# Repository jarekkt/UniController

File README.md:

# UniController

This is a off-spin from my commercial controller for industrial ink printers.
It is designed for pick & place machines controlled by OpenPnp

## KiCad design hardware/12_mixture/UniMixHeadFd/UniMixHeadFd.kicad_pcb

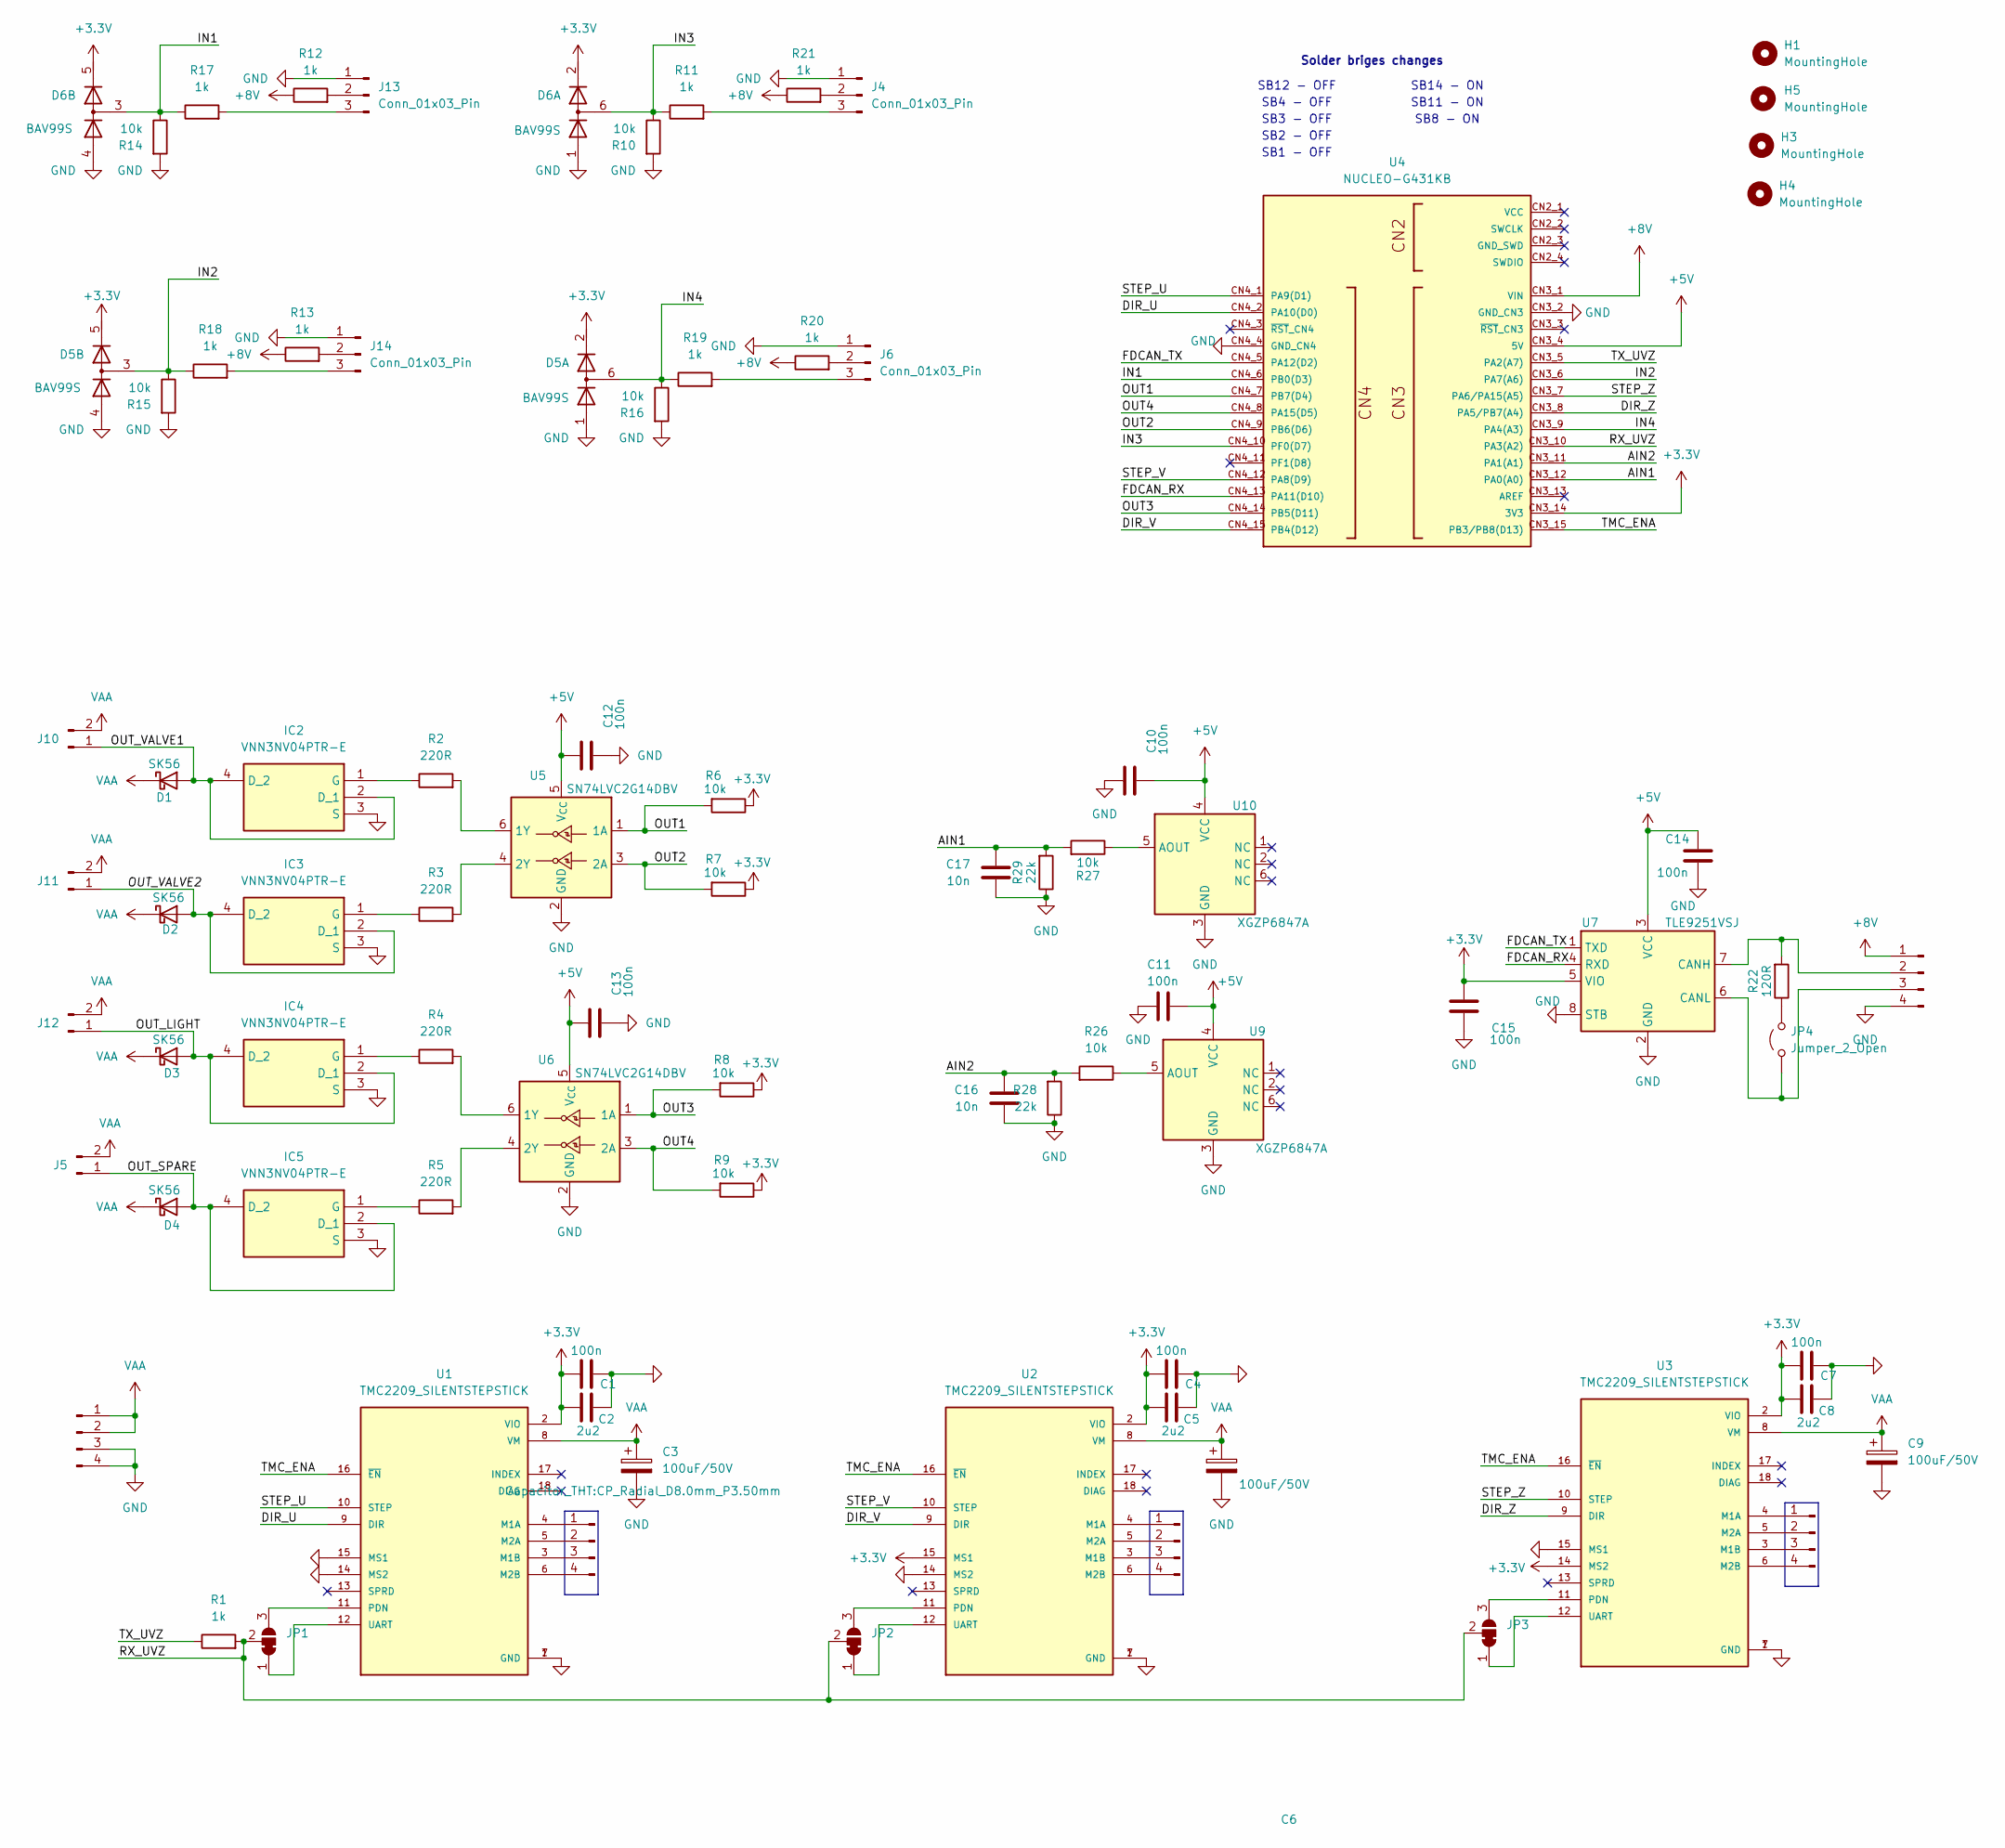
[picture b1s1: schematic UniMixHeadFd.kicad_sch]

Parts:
C1, C4, C7, C10, C11, C12, C13, C15: 100n; C_0603_1608Metric
C2, C5, C8: 2u2; C_0603_1608Metric
C3, C6, C9: 100uF/50V; CP_Radial_D8.0mm_P3.50mm
C14: 100n; C_0603_1608Metric; Digikey CC0402KRX7R7BB104
C16, C17: 10n; C_0603_1608Metric
D1, D2, D3, D4: SK56; D_SMB
D5, D6: BAV99S; SOT-363_SC-70-6
H1, H3, H4, H5: MountingHole; MountingHole_3.2mm_M3
IC2, IC3, IC4, IC5: VNN3NV04PTR-E; SOT230P700X180-4N; Manufacturer_Part_Number VNN3NV04PTR-E; Mouser Part Number 511-VNN3NV04PTR-E
J1, J2, J3, J25, J26: Conn_01x04_Male; JST_XH_B4B-XH-AM_1x04_P2.50mm_Vertical
J4, J6, J13, J14: Conn_01x03_Pin; JST_XH_B3B-XH-A_1x03_P2.50mm_Vertical
J5, J10, J11, J12: Conn_01x02_Male; JST_XH_B2B-XH-A_1x02_P2.50mm_Vertical
JP1, JP2, JP3: SolderJumper_3_Bridged12; SolderJumper-3_P1.3mm_Bridged12_RoundedPad1.0x1.5mm
JP4: Jumper_2_Open; SolderJumper-2_P1.3mm_Open_RoundedPad1.0x1.5mm
R1, R11, R12, R13, R17, R18, R19, R20, R21: 1k; R_0603_1608Metric
R2, R3, R4, R5: 220R; R_0603_1608Metric
R6, R7, R8, R9, R10, R14, R15, R16, R26, R27: 10k; R_0603_1608Metric
R22: 120R; R_1206_3216Metric
R28, R29: 22k; R_0603_1608Metric
U1, U2, U3: TMC2209_SILENTSTEPSTICK; MODULE_TMC2209_SILENTSTEPSTICK; PARTREV 1.20
U4: NUCLEO-G431KB; MODULE_NUCLEO-G431KB; PARTREV 2
U5, U6: SN74LVC2G14DBV; SOT-23-6
U7: TLE9251VSJ; SOIC-8_3.9x4.9mm_P1.27mm; Digikey TLE9251VSJXUMA1TR-ND
U9, U10: XGZP6847A; DIP-6_W10.16mm

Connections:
+3.3V: C1.2, C2.2, C4.2, C5.2, C7.2, C8.2, C15.1, D5.2 (K2), D5.5 (K4), D6.2 (K2), D6.5 (K4), R6.1, R7.1, R8.1, R9.1, U1.2 (VIO), U2.2 (VIO), U2.15 (MS1), U3.2 (VIO), U3.14 (MS2), U4.CN3_14 (3V3), U7.5 (VIO)
+5V: C10.2, C11.1, C12.1, C13.1, C14.1, U4.CN3_4 (5V), U5.5 (V_{CC}), U6.5 (V_{CC}), U7.3 (VCC), U9.4 (VCC), U10.4 (VCC)
+8V: J26.1, R12.1, R13.1, R20.1, R21.1, U4.CN3_1 (VIN)
/AIN1: C17.1, R27.2, R29.2, U4.CN3_12 (PA0(A0))
/AIN2: C16.1, R26.2, R28.2, U4.CN3_11 (PA1(A1))
/DIR_U: U1.9 (DIR), U4.CN4_2 (PA10(D0))
/DIR_V: U2.9 (DIR), U4.CN4_15 (PB4(D12))
/DIR_Z: U3.9 (DIR), U4.CN3_8 (PA5/PB7(A4))
/FDCAN_RX: U4.CN4_13 (PA11(D10)), U7.4 (RXD)
/FDCAN_TX: U4.CN4_5 (PA12(D2)), U7.1 (TXD)
/IN1: D6.3 (K1A2), R14.1, R17.1, U4.CN4_6 (PB0(D3))
/IN2: D5.3 (K1A2), R15.1, R18.1, U4.CN3_6 (PA7(A6))
/IN3: D6.6 (K3A4), R10.1, R11.1, U4.CN4_10 (PF0(D7))
/IN4: D5.6 (K3A4), R16.1, R19.1, U4.CN3_9 (PA4(A3))
/OUT1: R6.2, U4.CN4_7 (PB7(D4)), U5.1 (1A)
/OUT2: R7.2, U4.CN4_9 (PB6(D6)), U5.3 (2A)
/OUT3: R8.2, U4.CN4_14 (PB5(D11)), U6.1 (1A)
/OUT4: R9.2, U4.CN4_8 (PA15(D5)), U6.3 (2A)
/OUT_LIGHT: D3.2 (A), IC4.2 (D_1), IC4.4 (D_2), J12.1
/OUT_SPARE: D4.2 (A), IC5.2 (D_1), IC5.4 (D_2), J5.1
/OUT_VALVE1: D1.2 (A), IC2.2 (D_1), IC2.4 (D_2), J10.1
/OUT_VALVE2: D2.2 (A), IC3.2 (D_1), IC3.4 (D_2), J11.1
/RX_UVZ: JP1.2 (C), JP2.2 (C), JP3.2 (C), R1.2, U4.CN3_10 (PA3(A2))
/STEP_U: U1.10 (STEP), U4.CN4_1 (PA9(D1))
/STEP_V: U2.10 (STEP), U4.CN4_12 (PA8(D9))
/STEP_Z: U3.10 (STEP), U4.CN3_7 (PA6/PA15(A5))
/TMC_ENA: U1.16 (~EN), U2.16 (~EN), U3.16 (~EN), U4.CN3_15 (PB3/PB8(D13))
/TX_UVZ: R1.1, U4.CN3_5 (PA2(A7))
GND: C1.1, C2.1, C3.2, C4.1, C5.1, C6.2, C7.1, C8.1, C9.2, C10.1, C11.2, C12.2, C13.2, C14.2, C15.2, C16.2, C17.2, D5.1 (A1), D5.4 (A3), D6.1 (A1), D6.4 (A3), IC2.3 (S), IC3.3 (S), IC4.3 (S), IC5.3 (S), J4.1, J6.1, J13.1, J14.1, J25.3, J25.4, J26.4, R10.2, R14.2, R15.2, R16.2, R28.1, R29.1, U1.1 (GND), U1.7 (GND), U1.14 (MS2), U1.15 (MS1), U2.1 (GND), U2.7 (GND), U2.14 (MS2), U3.1 (GND), U3.7 (GND), U3.15 (MS1), U4.CN3_2 (GND_CN3), U4.CN4_4 (GND_CN4), U5.2 (GND), U6.2 (GND), U7.2 (GND), U7.8 (STB), U9.3 (GND), U10.3 (GND)
unnamed: IC2.1 (G), R2.1
unnamed: IC3.1 (G), R3.1
unnamed: IC4.1 (G), R4.1
unnamed: IC5.1 (G), R5.1
unnamed: J1.1, U1.4 (M1A)
unnamed: J1.2, U1.5 (M2A)
unnamed: J1.3, U1.3 (M1B)
unnamed: J1.4, U1.6 (M2B)
unnamed: J2.1, U2.4 (M1A)
unnamed: J2.2, U2.5 (M2A)
unnamed: J2.3, U2.3 (M1B)
unnamed: J2.4, U2.6 (M2B)
unnamed: J3.1, U3.4 (M1A)
unnamed: J3.2, U3.5 (M2A)
unnamed: J3.3, U3.3 (M1B)
unnamed: J3.4, U3.6 (M2B)
unnamed: J4.2, R21.2
unnamed: J4.3, R11.2
unnamed: J6.2, R20.2
unnamed: J6.3, R19.2
unnamed: J13.2, R12.2
unnamed: J13.3, R17.2
unnamed: J14.2, R13.2
unnamed: J14.3, R18.2
unnamed: J26.2, R22.2, U7.7 (CANH)
unnamed: J26.3, JP4.1 (A), U7.6 (CANL)
unnamed: JP1.1 (A), U1.12 (UART)
unnamed: JP1.3 (B), U1.11 (PDN)
unnamed: JP2.1 (A), U2.12 (UART)
unnamed: JP2.3 (B), U2.11 (PDN)
unnamed: JP3.1 (A), U3.12 (UART)
unnamed: JP3.3 (B), U3.11 (PDN)
unnamed: JP4.2 (B), R22.1
unnamed: R2.2, U5.6 (1Y)
unnamed: R3.2, U5.4 (2Y)
unnamed: R4.2, U6.6 (1Y)
unnamed: R5.2, U6.4 (2Y)
unnamed: R26.1, U9.5 (AOUT)
unnamed: R27.1, U10.5 (AOUT)
VAA: C3.1, C6.1, C9.1, D1.1 (K), D2.1 (K), D3.1 (K), D4.1 (K), J5.2, J10.2, J11.2, J12.2, J25.1, J25.2, U1.8 (VM), U2.8 (VM), U3.8 (VM)

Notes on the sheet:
SB8 - ON
SB3 - OFF
SB14 - ON
SB1 - OFF
SB11 - ON
SB4 - OFF
SB2 - OFF
SB12 - OFF
Solder briges changes

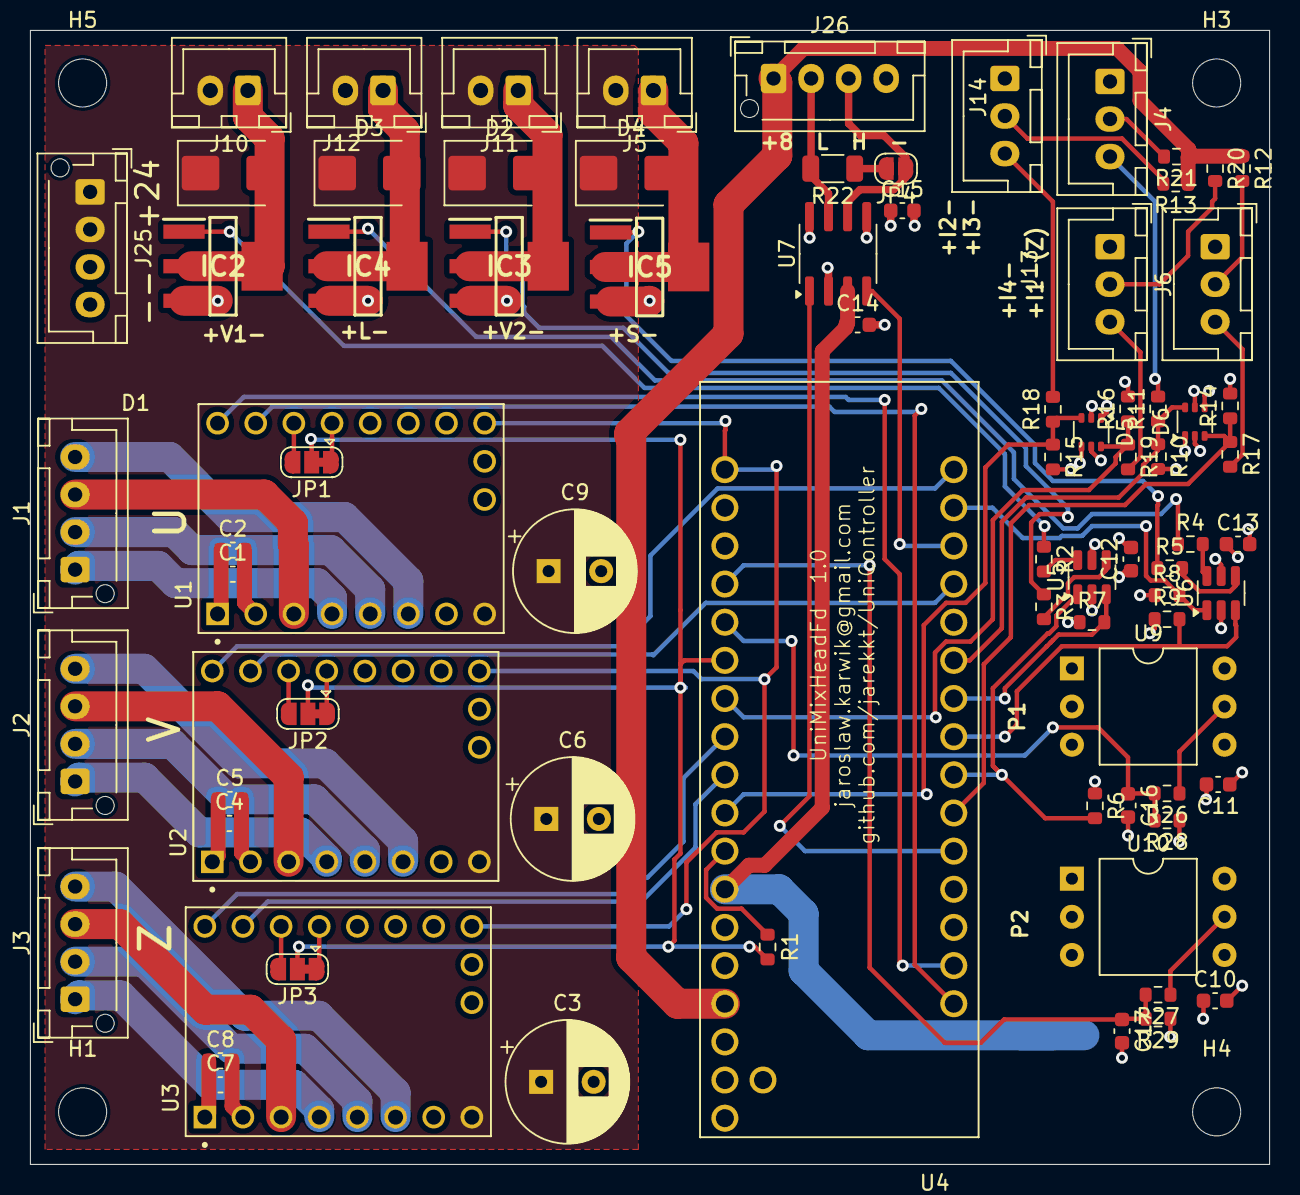
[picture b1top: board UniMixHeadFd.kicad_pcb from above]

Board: 4 copper layers, 82.5 x 75.5 mm, 83 parts (0 on the bottom side), 69 nets.

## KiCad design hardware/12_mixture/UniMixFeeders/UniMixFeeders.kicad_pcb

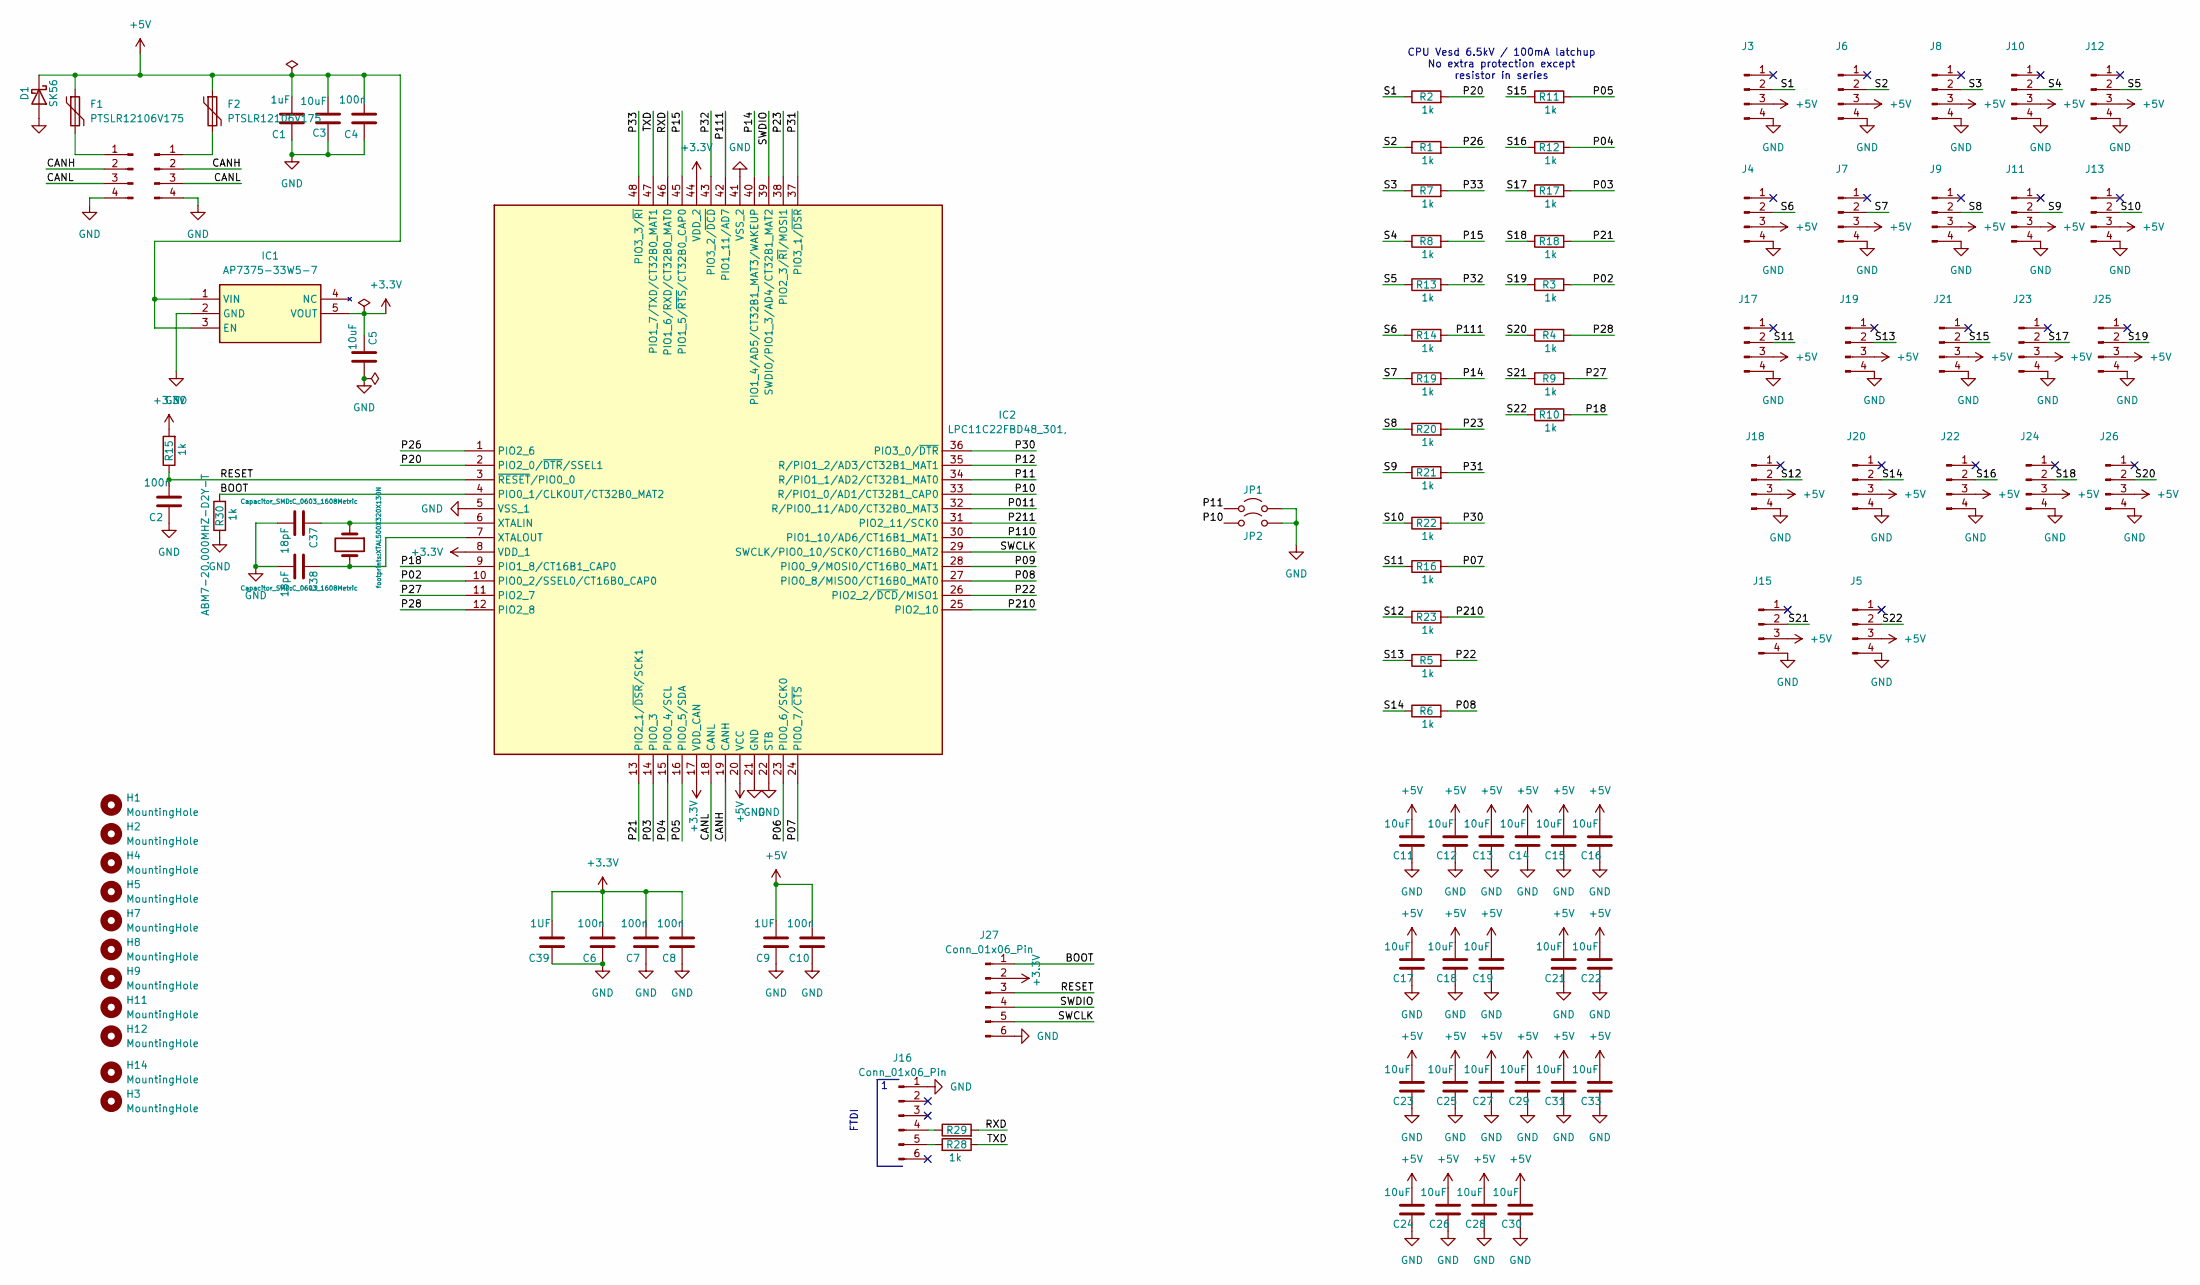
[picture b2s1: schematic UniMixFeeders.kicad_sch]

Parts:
C1: 1uF; C_0603_1608Metric
C2, C4, C6, C7, C8, C10: 100n; C_0603_1608Metric
C3, C5, C11, C12, C13, C14, C15, C16, C17, C18, C19, C21, C22, C23, C24, C25, C26, C27, C28, C29, C30, C31, C33: 10uF; C_1206_3216Metric
C9, C39: 1UF; C_0603_1608Metric
C37, C38: 18pF; C_0603_1608Metric
D1: SK56; D_SMB
F1, F2: PTSLR12106V175; Fuse_1210_3225Metric
H1, H2, H3, H4, H5, H7, H8, H9, H11, H12, H14: MountingHole; MountingHole_3.2mm_M3
IC1: AP7375-33W5-7; SOT95P285X140-5N
IC2: LPC11C22FBD48_301,; QFP50P900X900X160-48N; Manufacturer_Part_Number LPC11C22FBD48/301,; Mouser Part Number 771-LPC11C22FBD4830
J1, J2: Conn_01x04_Male; JST_XH_B4B-XH-AM_1x04_P2.50mm_Vertical
J3, J4, J5, J6, J7, J8, J9, J10, J11, J12, J13, J15, J17, J18, J19, J20, J21, J22, J23, J24, J25, J26: Conn_01x04_Pin; PinHeader_1x04_P2.54mm_Vertical
J16: Conn_01x06_Pin; PinHeader_1x06_P2.54mm_Vertical
J27: Conn_01x06_Pin; PinHeader_2x03_P2.54mm_Vertical
JP1, JP2: Jumper_2_Open; SolderJumper-2_P1.3mm_Open_RoundedPad1.0x1.5mm
R1, R2, R3, R4, R5, R6, R7, R8, R9, R10, R11, R12, R13, R14, R15, R16, R17, R18, R19, R20, R21, R22, R23, R28, R29, R30: 1k; R_0603_1608Metric
Y1: ABM7-20.000MHZ-D2Y-T; XTAL500X320X130N; Digikey 535-9843-2-ND

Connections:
+3.3V: C5.1, C6.1, C7.1, C8.1, C39.1, IC1.5 (VOUT), IC2.8 (VDD_1), IC2.17 (VDD_CAN), IC2.44 (VDD_2), J27.2, R15.2
+5V: C1.1, C3.1, C4.1, C9.1, C10.1, C11.1, C12.1, C13.1, C14.1, C15.1, C16.1, C17.1, C18.1, C19.1, C21.1, C22.1, C23.1, C24.1, C25.1, C26.1, C27.1, C28.1, C29.1, C30.1, C31.1, C33.1, D1.1 (K), F1.1, F2.1, IC1.1 (VIN), IC1.3 (EN), IC2.20 (VCC), J3.3, J4.3, J5.3, J6.3, J7.3, J8.3, J9.3, J10.3, J11.3, J12.3, J13.3, J15.3, J17.3, J18.3, J19.3, J20.3, J21.3, J22.3, J23.3, J24.3, J25.3, J26.3
/BOOT: IC2.4 (PIO0_1/CLKOUT/CT32B0_MAT2), J27.1, R30.2
/CANH: IC2.19 (CANH), J1.2, J2.2
/CANL: IC2.18 (CANL), J1.3, J2.3
/P02: IC2.10 (PIO0_2/SSEL0/CT16B0_CAP0), R3.2
/P03: IC2.14 (PIO0_3), R17.2
/P04: IC2.15 (PIO0_4/SCL), R12.2
/P05: IC2.16 (PIO0_5/SDA), R11.2
/P06: IC2.23 (PIO0_6/SCK0)
/P07: IC2.24 (PIO0_7/~CTS), R16.2
/P08: IC2.27 (PIO0_8/MISO0/CT16B0_MAT0), R6.2
/P09: IC2.28 (PIO0_9/MOSI0/CT16B0_MAT1)
/P10: IC2.33 (R/PIO1_0/AD1/CT32B1_CAP0), JP2.1 (A)
/P011: IC2.32 (R/PIO0_11/AD0/CT32B0_MAT3)
/P11: IC2.34 (R/PIO1_1/AD2/CT32B1_MAT0), JP1.1 (A)
/P12: IC2.35 (R/PIO1_2/AD3/CT32B1_MAT1)
/P14: IC2.40 (PIO1_4/AD5/CT32B1_MAT3/WAKEUP), R19.2
/P15: IC2.45 (PIO1_5/~RTS/CT32B0_CAP0), R8.2
/P18: IC2.9 (PIO1_8/CT16B1_CAP0), R10.2
/P20: IC2.2 (PIO2_0/~DTR/SSEL1), R2.2
/P21: IC2.13 (PIO2_1/~DSR/SCK1), R18.2
/P22: IC2.26 (PIO2_2/~DCD/MISO1), R5.2
/P23: IC2.38 (PIO2_3/~RI/MOSI1), R20.2
/P26: IC2.1 (PIO2_6), R1.2
/P27: IC2.11 (PIO2_7), R9.2
/P28: IC2.12 (PIO2_8), R4.2
/P30: IC2.36 (PIO3_0/~DTR), R22.2
/P31: IC2.37 (PIO3_1/~DSR), R21.2
/P32: IC2.43 (PIO3_2/~DCD), R13.2
/P33: IC2.48 (PIO3_3/~RI), R7.2
/P110: IC2.30 (PIO1_10/AD6/CT16B1_MAT1)
/P111: IC2.42 (PIO1_11/AD7), R14.2
/P210: IC2.25 (PIO2_10), R23.2
/P211: IC2.31 (PIO2_11/SCK0)
/RESET: C2.1, IC2.3 (~RESET/PIO0_0), J27.3, R15.1
/RXD: IC2.46 (PIO1_6/RXD/CT32B0_MAT0), R29.2
/S1: J3.2, R2.1
/S2: J6.2, R1.1
/S3: J8.2, R7.1
/S4: J10.2, R8.1
/S5: J12.2, R13.1
/S6: J4.2, R14.1
/S7: J7.2, R19.1
/S8: J9.2, R20.1
/S9: J11.2, R21.1
/S10: J13.2, R22.1
/S11: J17.2, R16.1
/S12: J18.2, R23.1
/S13: J19.2, R5.1
/S14: J20.2, R6.1
/S15: J21.2, R11.1
/S16: J22.2, R12.1
/S17: J23.2, R17.1
/S18: J24.2, R18.1
/S19: J25.2, R3.1
/S20: J26.2, R4.1
/S21: J15.2, R9.1
/S22: J5.2, R10.1
/SWCLK: IC2.29 (SWCLK/PIO0_10/SCK0/CT16B0_MAT2), J27.5
/SWDIO: IC2.39 (SWDIO/PIO1_3/AD4/CT32B1_MAT2), J27.4
/TXD: IC2.47 (PIO1_7/TXD/CT32B0_MAT1), R28.1
GND: C1.2, C2.2, C3.2, C4.2, C5.2, C6.2, C7.2, C8.2, C9.2, C10.2, C11.2, C12.2, C13.2, C14.2, C15.2, C16.2, C17.2, C18.2, C19.2, C21.2, C22.2, C23.2, C24.2, C25.2, C26.2, C27.2, C28.2, C29.2, C30.2, C31.2, C33.2, C37.2, C38.2, C39.2, D1.2 (A), IC1.2 (GND), IC2.5 (VSS_1), IC2.21 (GND), IC2.22 (STB), IC2.41 (VSS_2), J1.4, J2.4, J3.4, J4.4, J5.4, J6.4, J7.4, J8.4, J9.4, J10.4, J11.4, J12.4, J13.4, J15.4, J16.1, J17.4, J18.4, J19.4, J20.4, J21.4, J22.4, J23.4, J24.4, J25.4, J26.4, J27.6, JP1.2 (B), JP2.2 (B), R30.1
unnamed: C37.1, IC2.6 (XTALIN), Y1.1
unnamed: C38.1, IC2.7 (XTALOUT), Y1.2
unnamed: F1.2, J1.1
unnamed: F2.2, J2.1
unnamed: J16.4, R29.1
unnamed: J16.5, R28.2

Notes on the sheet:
CPU Vesd 6.5kV / 100mA latchup No extra protection except resistor in series
FTDI

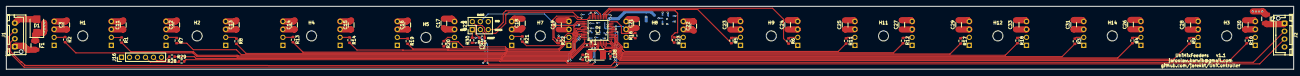
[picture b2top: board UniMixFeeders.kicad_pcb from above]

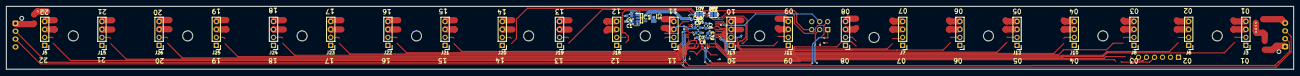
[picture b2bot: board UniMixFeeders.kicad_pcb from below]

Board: 4 copper layers, 409.6 x 20.0 mm, 105 parts (34 on the bottom side), 63 nets.
